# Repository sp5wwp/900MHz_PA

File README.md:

# 900MHz_PA
900MHz-band power amplifier with RA45H8994M1 module

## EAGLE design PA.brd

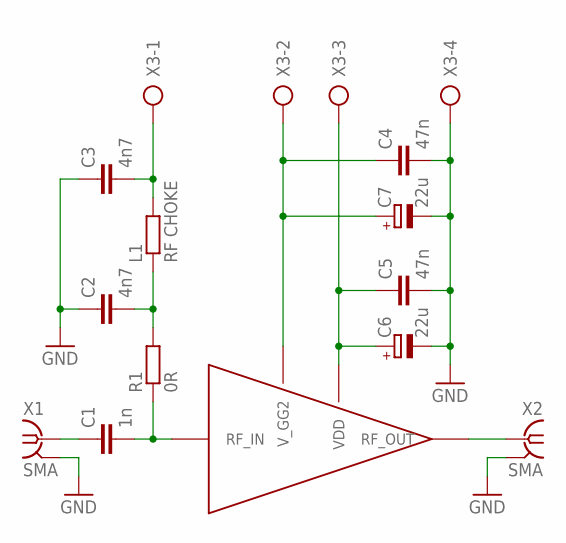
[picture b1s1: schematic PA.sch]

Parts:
C1: 1n; C0805K
C2, C3: 4n7; C0805K
C4, C5: 47n; C1206K
C6, C7: 22u; 153CLV-1010
L1: RF CHOKE; R0805
R1: 0R; R0805
U$1: RA45H8994M1; RF_MODULE
X1, X2: SMA; J502-ND-142-0701-801/806
X3: AK500/4

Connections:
GND: C2.1, C3.1, C4.2, C5.2, C6.-, C7.-, X1.G@1 (2), X1.G@2 (2), X1.G@3 (2), X1.G@4 (2), X2.G@1 (2), X2.G@2 (2), X2.G@3 (2), X2.G@4 (2), X3.4
unnamed: C1.1, X1.1
unnamed: C1.2, R1.1, U$1.RF_IN
unnamed: U$1.RF_OUT, X2.1
unnamed: C2.2, L1.1, R1.2
unnamed: C3.2, L1.2, X3.1
unnamed: C4.1, C7.+, U$1.V_GG2, X3.2
unnamed: C5.1, C6.+, U$1.VDD, X3.3

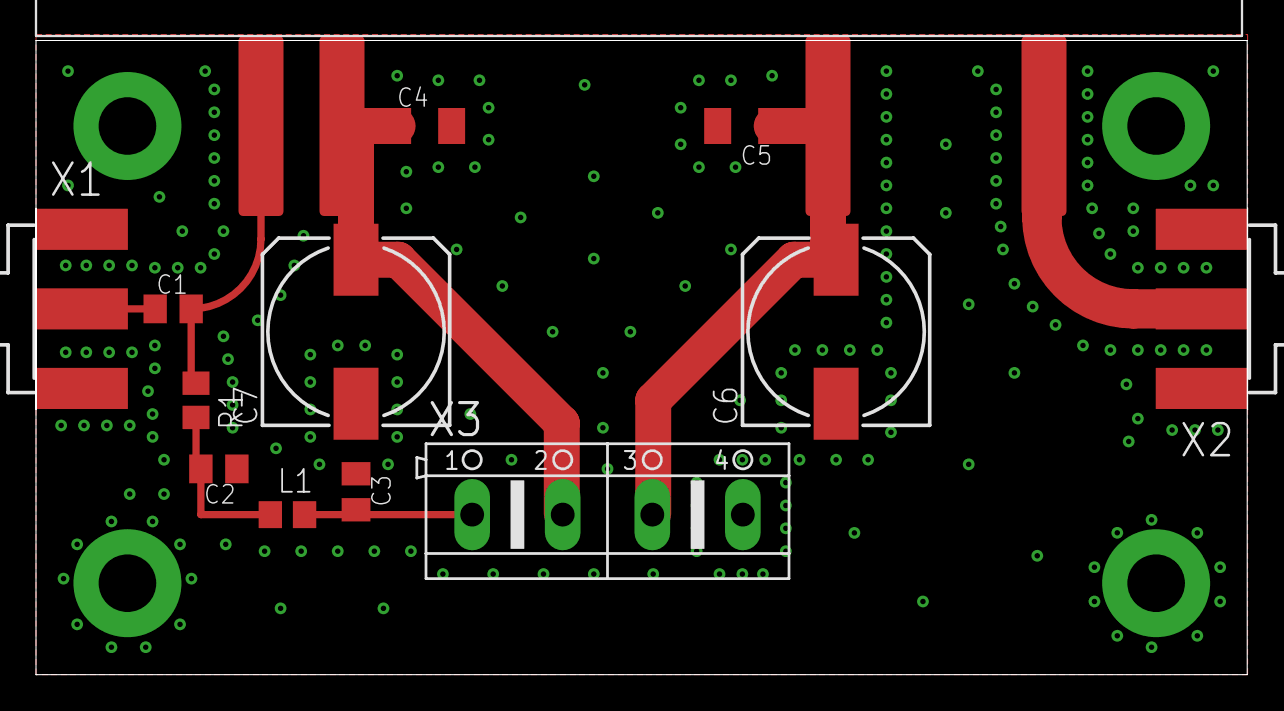
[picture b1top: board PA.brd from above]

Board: 2 copper layers, 67.3 x 35.2 mm, 13 parts (0 on the bottom side), 8 nets.
